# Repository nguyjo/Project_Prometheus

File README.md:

# Walla Walla University Prometheus Rocket Project (2025-2026)

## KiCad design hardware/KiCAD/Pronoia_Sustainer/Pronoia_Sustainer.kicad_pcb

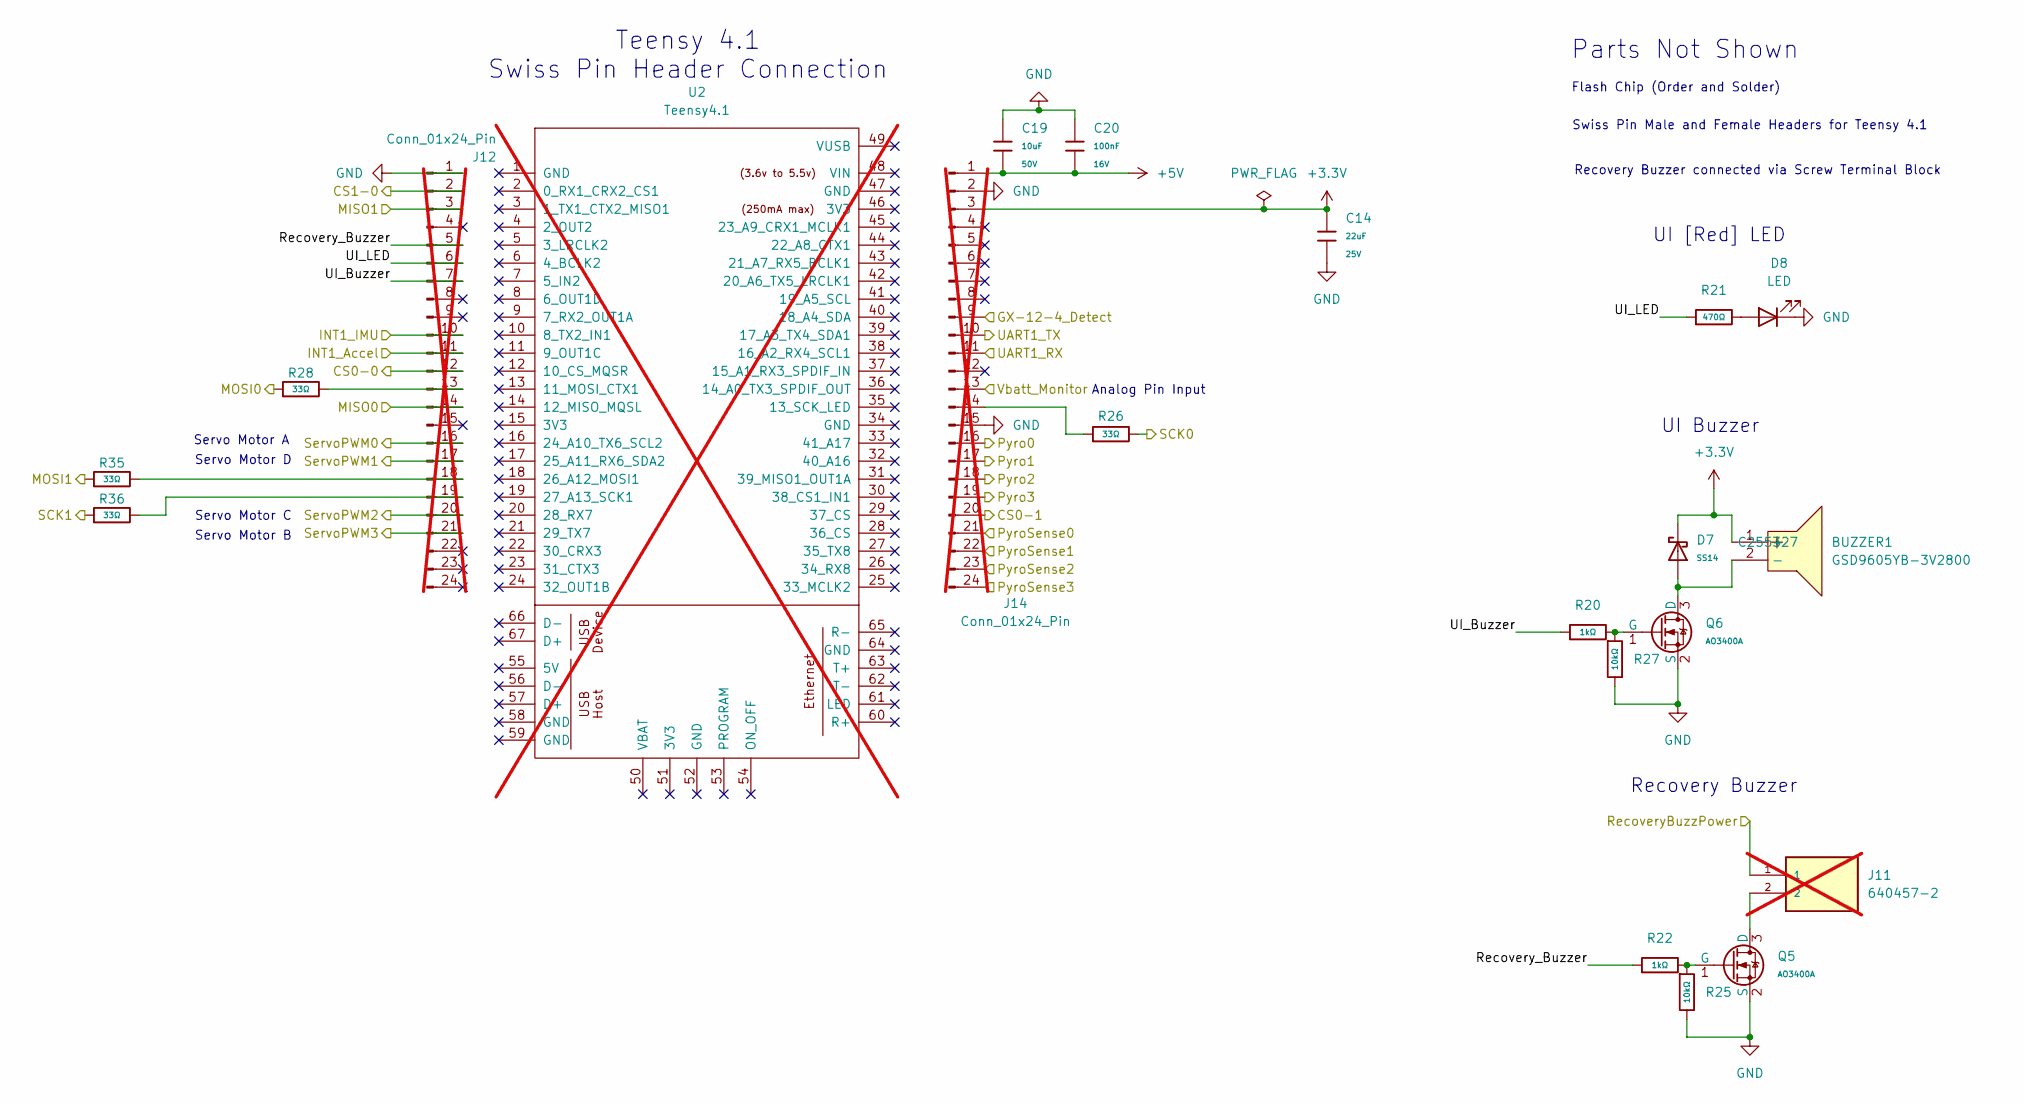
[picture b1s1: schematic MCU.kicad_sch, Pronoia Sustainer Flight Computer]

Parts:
BUZZER1: GSD9605YB-3V2800; BUZ-SMD_GSD9605YB-3V2800; LCSC C255327
C14: 22uF; C_0805; Voltage Rated 25V; Tolerance ±20%; Part CL21A226MAQNNNE; LCSC C45783
C19: 10uF; C_1206; Voltage Rated 50V; Tolerance ±10%; Part CL31A106KBHNNNE; LCSC C13585
C20: 100nF; C_0402; Voltage Rated 16V; Tolerance ±10%; Part CL05B104KO5NNNC; LCSC C1525
D7: SS14; D_SMA; Forward Voltage (Vf@If) 550mV@1A; Reverse Voltage (Vr) 40V; Part SS14; LCSC C2480
D8: LED; LED_0603_1608Metric; LCSC C3030991
J11: 640457-2; TE_640457-2; PARTREV R; not fitted
J12, J14: Conn_01x24_Pin; PinSocket_1x24_P2.54mm_Vertical; not fitted
Q5, Q6: AO3400A; Q_SOT-23; Part AO3400A; LCSC C20917
R20, R22: 1kΩ; R_0805; Overload Voltage (Max) 150V; Tolerance ±1%; Part 0805W8F1001T5E; LCSC C17513
R21: 470Ω; R_0402; Overload Voltage (Max) 50V; Tolerance ±1%; Part 0402WGF4700TCE; LCSC C25117
R25, R27: 10kΩ; R_0805; Overload Voltage (Max) 150V; Tolerance ±1%; Part 0805W8F1002T5E; LCSC C17414
R26, R28, R35, R36: 33Ω; R_0402; Overload Voltage (Max) 50V; Tolerance ±1%; Part 0402WGF330JTCE; LCSC C25105
U2: Teensy4.1; Teensy41; not fitted

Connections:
+3.3V: BUZZER1.1 (+), C14.1, D7.1, J14.3; also elsewhere on the board
+5V: C19.2, C20.1, J14.1; also elsewhere on the board
/Communications/GX-12-4_Detect: J14.9; also elsewhere on the board
/Communications/GX-12-4_RX: J14.10; also elsewhere on the board
/Communications/GX-12-4_TX: J14.11; also elsewhere on the board
/Flight Computer/CS0-0: J12.12; also elsewhere on the board
/Flight Computer/CS0-1: J14.20; also elsewhere on the board
/Flight Computer/CS1-0: J12.2; also elsewhere on the board
/Flight Computer/INT1_Accel: J12.11; also elsewhere on the board
/Flight Computer/INT1_IMU: J12.10; also elsewhere on the board
/Flight Computer/MISO0: J12.14; also elsewhere on the board
/Flight Computer/MISO1: J12.3; also elsewhere on the board
/Flight Computer/MOSI0: R28.1; also elsewhere on the board
/Flight Computer/MOSI1: R35.1; also elsewhere on the board
/Flight Computer/Pyro0: J14.16; also elsewhere on the board
/Flight Computer/Pyro1: J14.17; also elsewhere on the board
/Flight Computer/Pyro2: J14.18; also elsewhere on the board
/Flight Computer/Pyro3: J14.19; also elsewhere on the board
/Flight Computer/PyroSense0: J14.21; also elsewhere on the board
/Flight Computer/PyroSense1: J14.22; also elsewhere on the board
/Flight Computer/PyroSense2: J14.23; also elsewhere on the board
/Flight Computer/PyroSense3: J14.24; also elsewhere on the board
/Flight Computer/RecoveryBuzzPower: J11.1; also elsewhere on the board
/Flight Computer/Recovery_Buzzer: J12.5, R22.1
/Flight Computer/SCK0: R26.2; also elsewhere on the board
/Flight Computer/SCK1: R36.1; also elsewhere on the board
/Flight Computer/ServoPWM0: J12.16; also elsewhere on the board
/Flight Computer/ServoPWM1: J12.17; also elsewhere on the board
/Flight Computer/ServoPWM2: J12.20; also elsewhere on the board
/Flight Computer/ServoPWM3: J12.21; also elsewhere on the board
/Flight Computer/UI_Buzzer: J12.7, R20.1
/Flight Computer/UI_LED: J12.6, R21.1
/Flight Computer/Vbatt_Monitor: J14.13; also elsewhere on the board
GND: C14.2, C19.1, C20.2, D8.1 (K), J12.1, J14.2, J14.15, Q5.2 (S), Q6.2 (S), R25.2, R27.2; also elsewhere on the board
unnamed: BUZZER1.2 (-), D7.2, Q6.3 (D)
unnamed: D8.2 (A), R21.2
unnamed: J12.13, R28.2
unnamed: J12.18, R35.2
unnamed: J12.19, R36.2
unnamed: J14.14, R26.1
unnamed: J11.2, Q5.3 (D)
unnamed: Q5.1 (G), R22.2, R25.1
unnamed: Q6.1 (G), R20.2, R27.1

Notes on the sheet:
Parts Not Shown
Recovery Buzzer connected via Screw Terminal Block
Servo Motor C
Analog Pin Input
Swiss Pin Male and Female Headers for Teensy 4.1
Servo Motor D
Teensy 4.1 Swiss Pin Header Connection
Servo Motor B
Servo Motor A
UI [Red] LED
Flash Chip (Order and Solder)
Recovery Buzzer
UI Buzzer

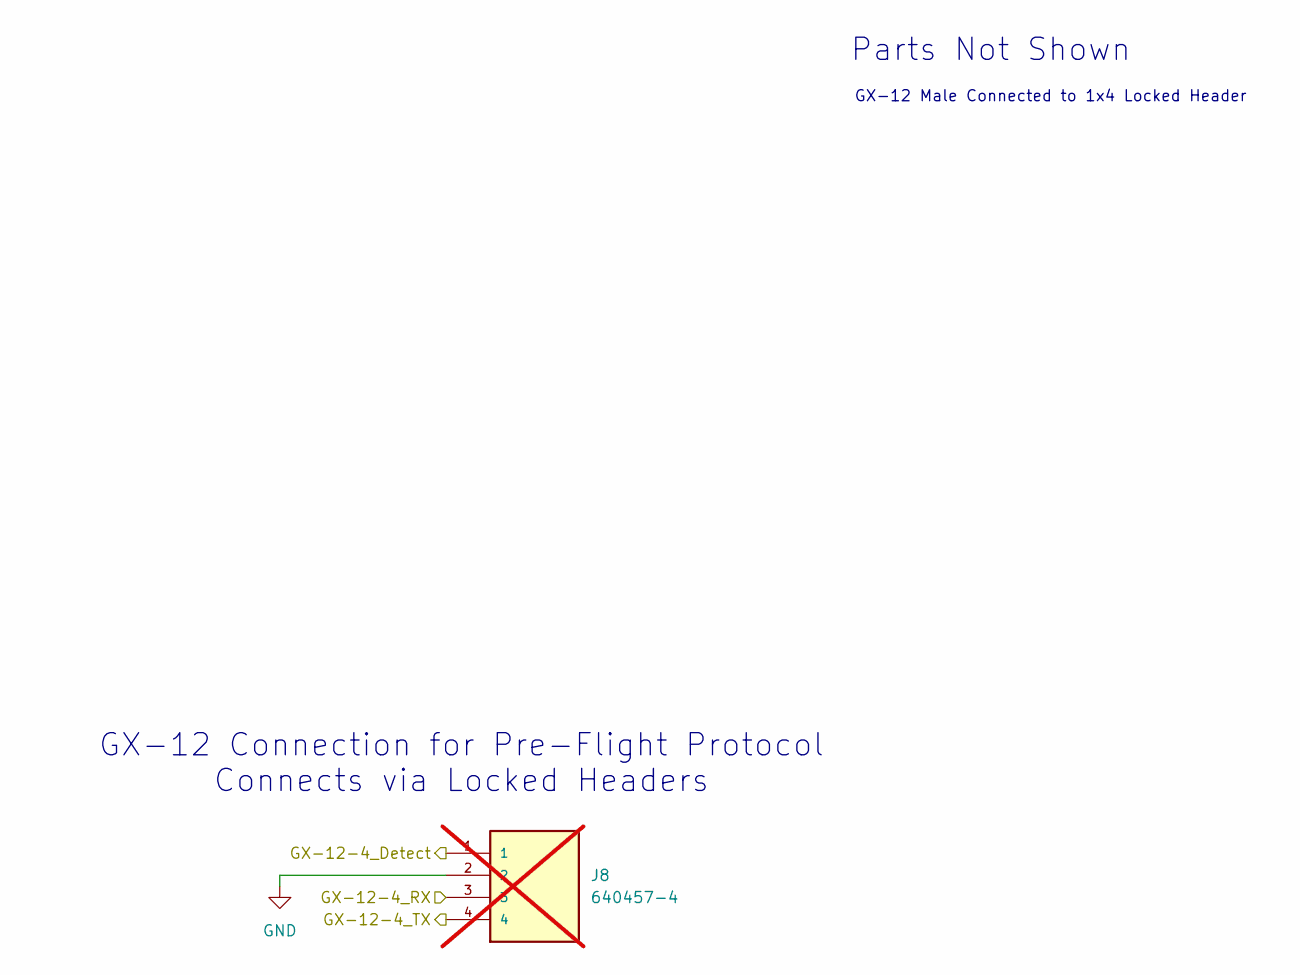
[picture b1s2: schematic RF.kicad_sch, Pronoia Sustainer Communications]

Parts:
J8: 640457-4; TE_640457-4; PARTREV R; not fitted

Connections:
/Communications/GX-12-4_Detect: J8.1; also elsewhere on the board
/Communications/GX-12-4_RX: J8.3; also elsewhere on the board
/Communications/GX-12-4_TX: J8.4; also elsewhere on the board
GND: J8.2; also elsewhere on the board

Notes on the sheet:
GX-12 Connection for Pre-Flight Protocol Connects via Locked Headers
Parts Not Shown
GX-12 Male Connected to 1x4 Locked Header

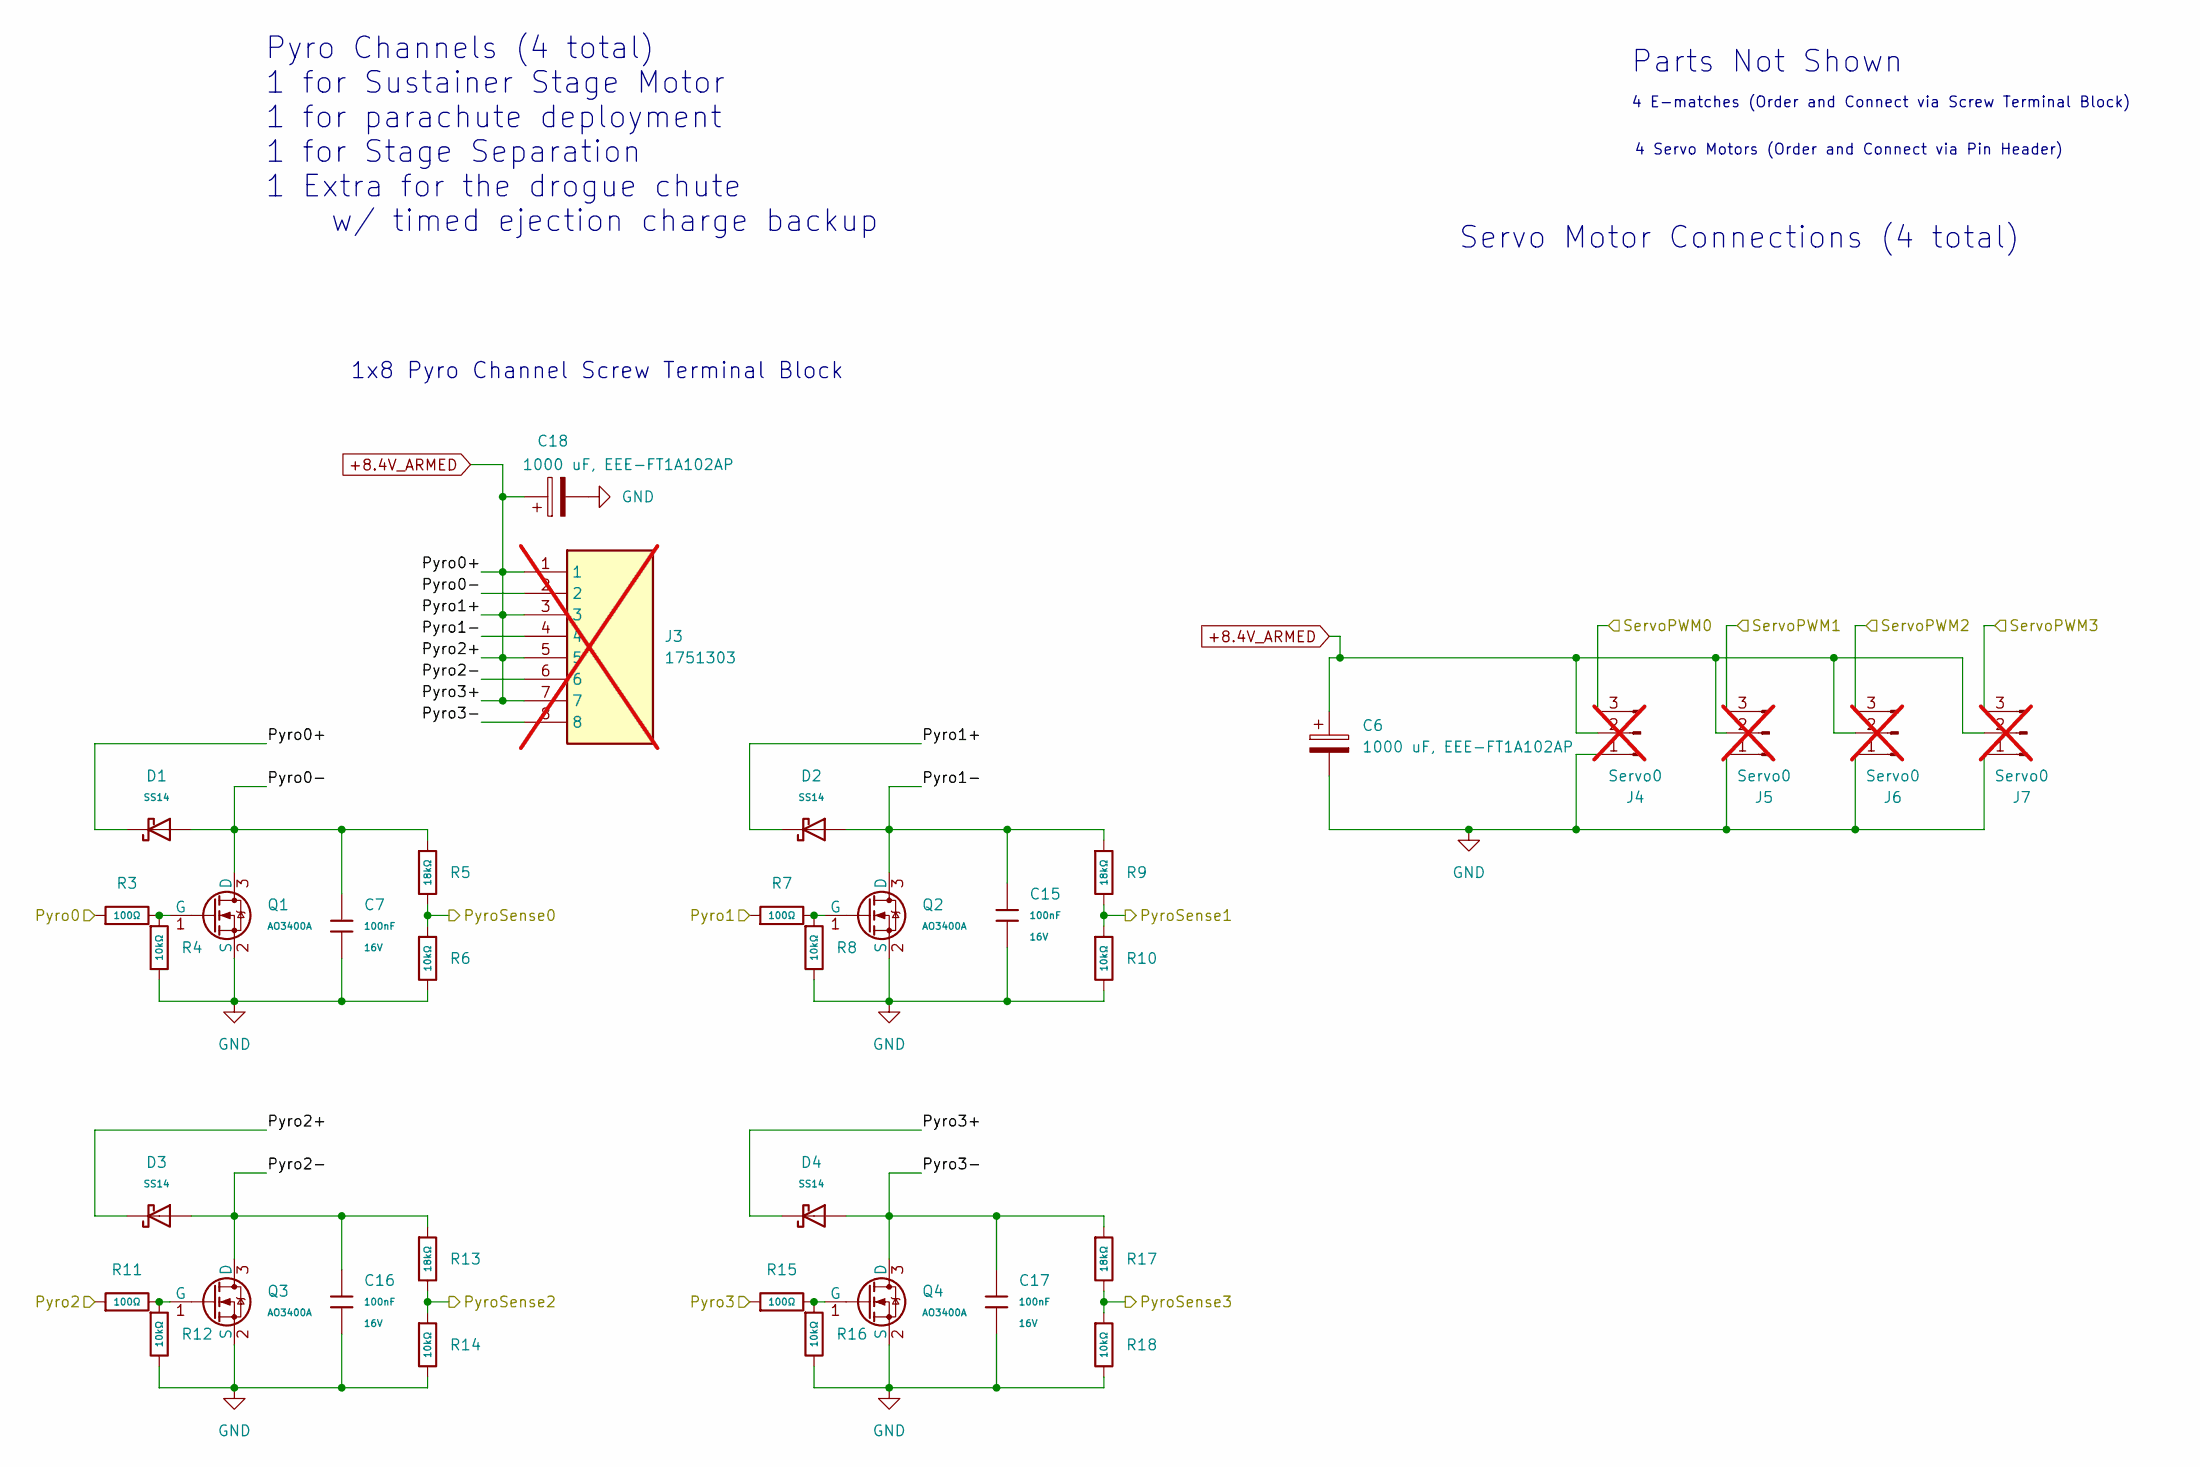
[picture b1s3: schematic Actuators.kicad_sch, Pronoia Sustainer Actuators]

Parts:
C6, C18: 1000 uF, EEE-FT1A102AP; CP_Elec_8x10.5; LCSC C278408
C7, C15, C16, C17: 100nF; C_0402; Voltage Rated 16V; Tolerance ±10%; Part CL05B104KO5NNNC; LCSC C1525
D1, D2, D3, D4: SS14; D_SMA; Forward Voltage (Vf@If) 550mV@1A; Reverse Voltage (Vr) 40V; Part SS14; LCSC C2480
J3: 1751303; Manufacturer_Part_Number 1751303; Mouser Part Number 651-1751303; not fitted
J4, J5, J6, J7: Servo0; PinHeader_1x03_P2.54mm_Vertical; not fitted
Q1, Q2, Q3, Q4: AO3400A; Q_SOT-23; Part AO3400A; LCSC C20917
R3, R7, R11, R15: 100Ω; R_0805; Overload Voltage (Max) 150V; Tolerance ±1%; Part 0805W8F1000T5E; LCSC C17408
R4, R6, R8, R10, R12, R14, R16, R18: 10kΩ; R_0805; Overload Voltage (Max) 150V; Tolerance ±1%; Part 0805W8F1002T5E; LCSC C17414
R5, R9, R13, R17: 18kΩ; R_0603; Overload Voltage (Max) 75V; Tolerance ±1%; Part 0603WAF1802T5E; LCSC C25810

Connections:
+8.4V_ARMED: C6.1, C18.1, D1.1, D2.1, D3.1, D4.1, J3.1, J3.3, J3.5, J3.7, J4.2, J5.2, J6.2, J7.2; also elsewhere on the board
/Flight Computer/Pyro0: R3.1; also elsewhere on the board
/Flight Computer/Pyro1: R7.1; also elsewhere on the board
/Flight Computer/Pyro2: R11.1; also elsewhere on the board
/Flight Computer/Pyro3: R15.1; also elsewhere on the board
/Flight Computer/PyroSense0: R5.2, R6.1; also elsewhere on the board
/Flight Computer/PyroSense1: R9.2, R10.1; also elsewhere on the board
/Flight Computer/PyroSense2: R13.2, R14.1; also elsewhere on the board
/Flight Computer/PyroSense3: R17.2, R18.1; also elsewhere on the board
/Flight Computer/ServoPWM0: J4.3; also elsewhere on the board
/Flight Computer/ServoPWM1: J5.3; also elsewhere on the board
/Flight Computer/ServoPWM2: J6.3; also elsewhere on the board
/Flight Computer/ServoPWM3: J7.3; also elsewhere on the board
/High-Power Actuators/Pyro0-: C7.1, D1.2, J3.2, Q1.3 (D), R5.1
/High-Power Actuators/Pyro1-: C15.1, D2.2, J3.4, Q2.3 (D), R9.1
/High-Power Actuators/Pyro2-: C16.1, D3.2, J3.6, Q3.3 (D), R13.1
/High-Power Actuators/Pyro3-: C17.1, D4.2, J3.8, Q4.3 (D), R17.1
GND: C6.2, C7.2, C15.2, C16.2, C17.2, C18.2, J4.1, J5.1, J6.1, J7.1, Q1.2 (S), Q2.2 (S), Q3.2 (S), Q4.2 (S), R4.2, R6.2, R8.2, R10.2, R12.2, R14.2, R16.2, R18.2; also elsewhere on the board
unnamed: Q1.1 (G), R3.2, R4.1
unnamed: Q2.1 (G), R7.2, R8.1
unnamed: Q3.1 (G), R11.2, R12.1
unnamed: Q4.1 (G), R15.2, R16.1

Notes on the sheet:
4 E-matches (Order and Connect via Screw Terminal Block)
Parts Not Shown
Pyro Channels (4 total) 1 for Sustainer Stage Motor 1 for parachute deployment 1 for Stage Separation 1 Extra for the drogue chute w/ timed ejection charge backup
1x8 Pyro Channel Screw Terminal Block
4 Servo Motors (Order and Connect via Pin Header)
Servo Motor Connections (4 total)

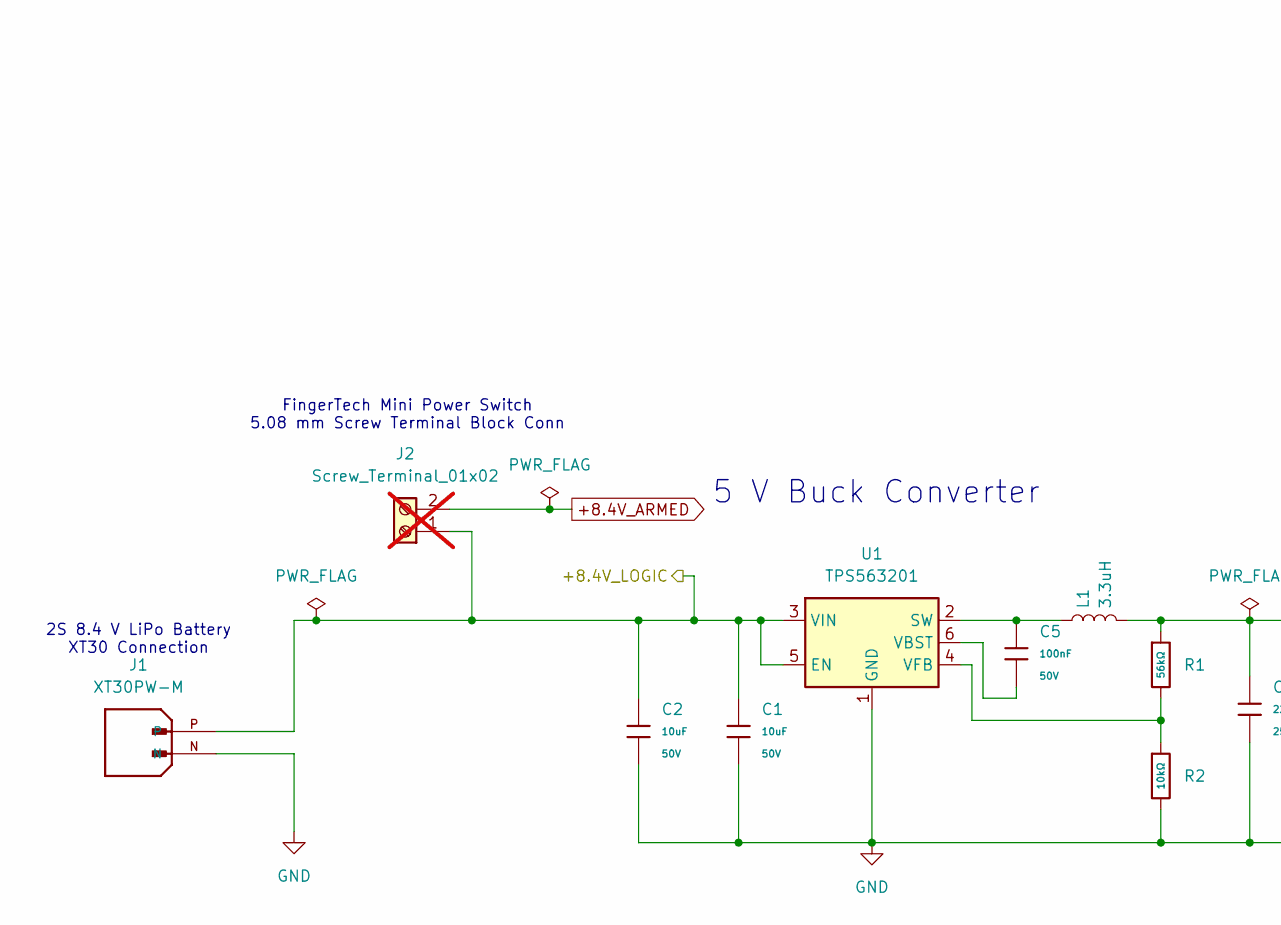
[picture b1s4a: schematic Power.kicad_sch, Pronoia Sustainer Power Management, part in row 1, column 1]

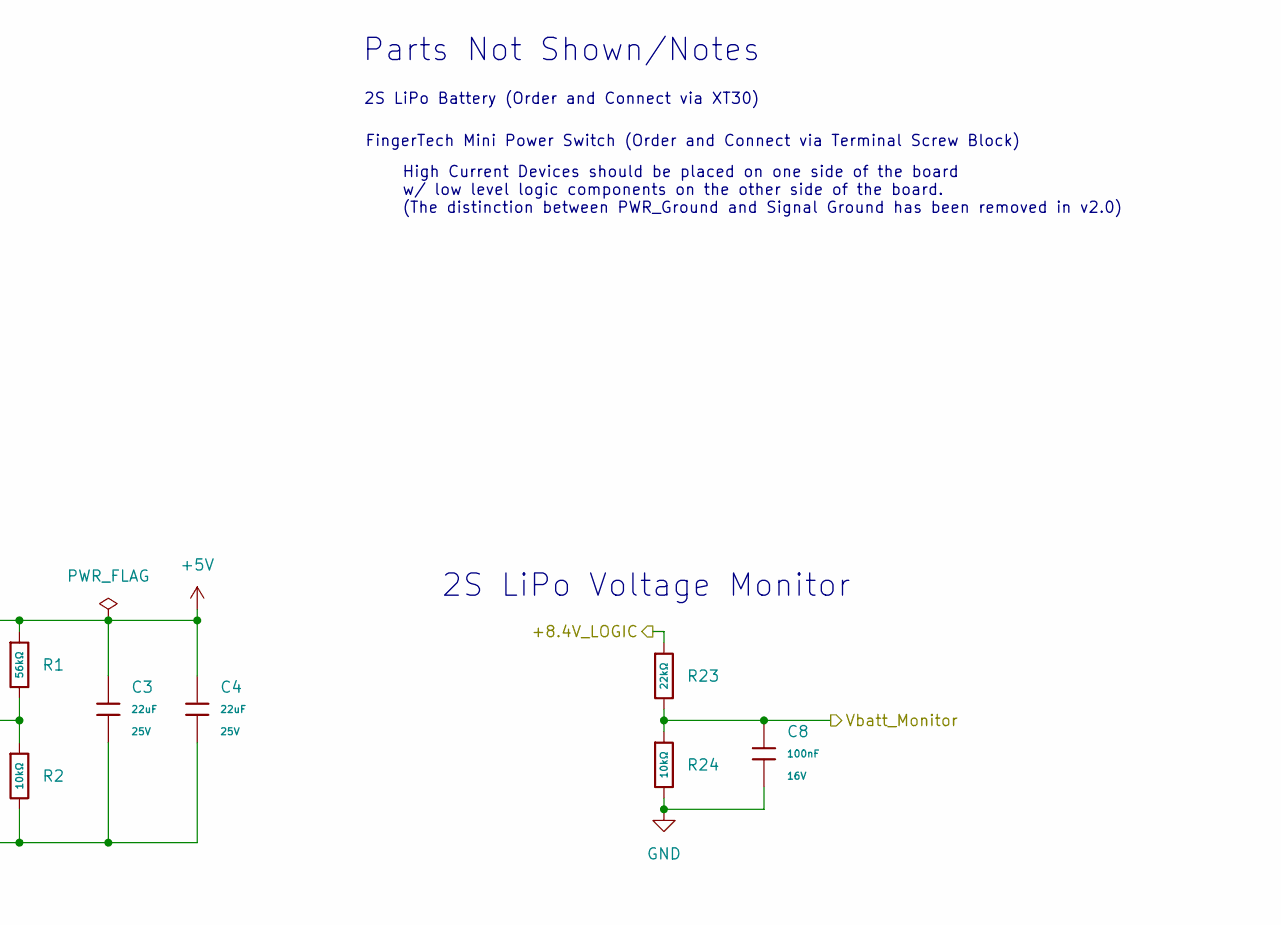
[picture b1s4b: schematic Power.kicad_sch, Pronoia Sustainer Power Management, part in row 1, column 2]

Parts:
C1, C2: 10uF; C_1206; Voltage Rated 50V; Tolerance ±10%; Part CL31A106KBHNNNE; LCSC C13585
C3, C4: 22uF; C_0805; Voltage Rated 25V; Tolerance ±20%; Part CL21A226MAQNNNE; LCSC C45783
C5: 100nF; C_1206; Voltage Rated 50V; Tolerance ±10%; Part CL31B104KBCNNNC; LCSC C24497
C8: 100nF; C_0402; Voltage Rated 16V; Tolerance ±10%; Part CL05B104KO5NNNC; LCSC C1525
J1: XT30PW-M; AMASS_XT30PW-M; PARTREV 1.2; LCSC C431092
J2: Screw_Terminal_01x02; TerminalBlock_Phoenix_MKDS-1,5-2-5.08_1x02_P5.08mm_Horizont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; not fitted
L1: 3.3uH; L_Bourns-SRN8040_8x8.15mm; LCSC C780188
R1: 56kΩ; R_0603; Overload Voltage (Max) 75V; Tolerance ±1%; Part 0603WAF5602T5E; LCSC C23206
R2: 10kΩ; R_0603; Overload Voltage (Max) 75V; Tolerance ±1%; Part 0603WAF1002T5E; LCSC C25804
R23: 22kΩ; R_0805; Overload Voltage (Max) 150V; Tolerance ±1%; Part 0805W8F2202T5E; LCSC C17560
R24: 10kΩ; R_0805; Overload Voltage (Max) 150V; Tolerance ±1%; Part 0805W8F1002T5E; LCSC C17414
U1: TPS563201; SOT-23-6; LCSC C116592

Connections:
+5V: C3.1, C4.1, L1.2, R1.1; also elsewhere on the board
+8.4V_ARMED: J2.2; also elsewhere on the board
/Flight Computer/RecoveryBuzzPower: C1.1, C2.1, J1.P, J2.1, R23.1, U1.3 (VIN), U1.5 (EN); also elsewhere on the board
/Flight Computer/Vbatt_Monitor: C8.1, R23.2, R24.1; also elsewhere on the board
GND: C1.2, C2.2, C3.2, C4.2, C8.2, J1.N, R2.2, R24.2, U1.1 (GND); also elsewhere on the board
unnamed: C5.1, L1.1, U1.2 (SW)
unnamed: C5.2, U1.6 (VBST)
unnamed: R1.2, R2.1, U1.4 (VFB)

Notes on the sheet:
5 V Buck Converter
FingerTech Mini Power Switch 5.08 mm Screw Terminal Block Conn
2S LiPo Voltage Monitor
High Current Devices should be placed on one side of the board w/ low level logic components on the other side of the board. (The distinction between PWR_Ground and Signal Ground has been removed in v2.0)
2S 8.4 V LiPo Battery XT30 Connection
2S LiPo Battery (Order and Connect via XT30)
FingerTech Mini Power Switch (Order and Connect via Terminal Screw Block)
Parts Not Shown/Notes

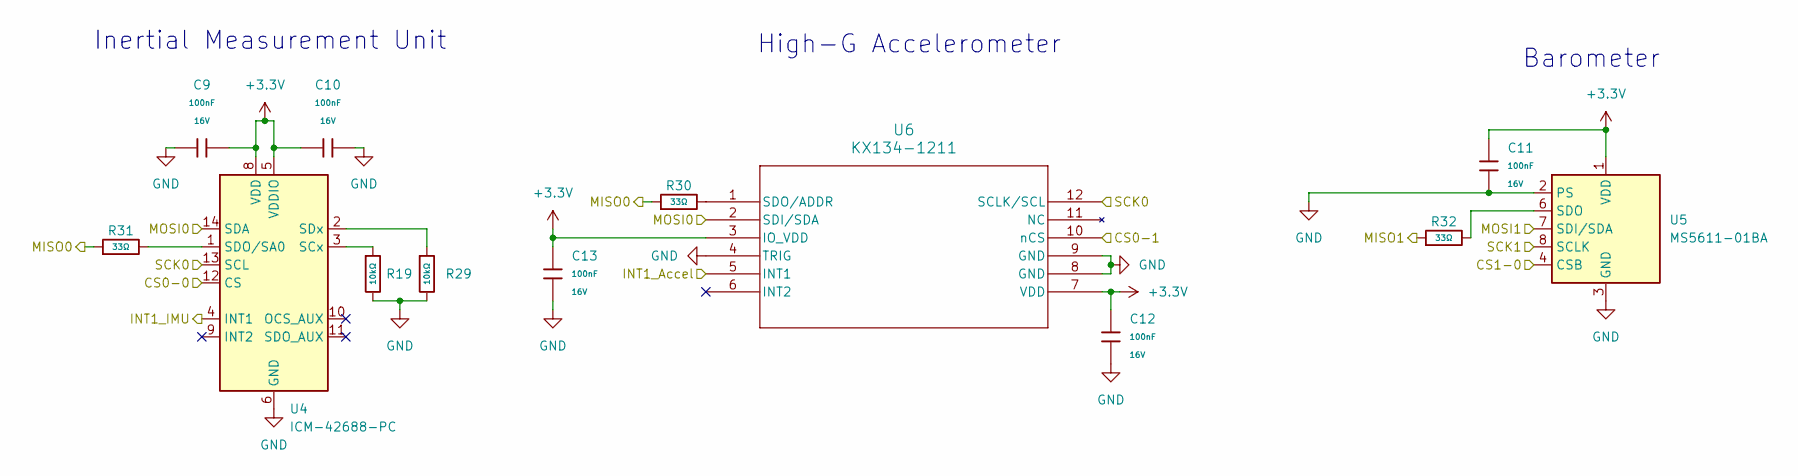
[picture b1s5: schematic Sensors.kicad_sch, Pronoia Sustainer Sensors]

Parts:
C9, C10, C11, C12, C13: 100nF; C_0402; Voltage Rated 16V; Tolerance ±10%; Part CL05B104KO5NNNC; LCSC C1525
R19, R29: 10kΩ; R_0805; Overload Voltage (Max) 150V; Tolerance ±1%; Part 0805W8F1002T5E; LCSC C17414
R30, R31, R32: 33Ω; R_0402; Overload Voltage (Max) 50V; Tolerance ±1%; Part 0402WGF330JTCE; LCSC C25105
U4: ICM-42688-PC; LGA-14_3x2.5mm_P0.5mm_LayoutBorder3x4y; LCSC C48586483
U5: MS5611-01BA; LGA-8_3x5mm_P1.25mm; LCSC C15639
U6: KX134-1211; KIONIX_KXTJ3-1057; LCSC C2157908

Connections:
+3.3V: C9.2, C10.1, C11.2, C12.2, C13.2, U4.5 (VDDIO), U4.8 (VDD), U5.1 (VDD), U6.3 (IO_VDD), U6.7 (VDD); also elsewhere on the board
/Flight Computer/CS0-0: U4.12 (CS); also elsewhere on the board
/Flight Computer/CS0-1: U6.10 (nCS); also elsewhere on the board
/Flight Computer/CS1-0: U5.4 (CSB), U5.5 (CSB); also elsewhere on the board
/Flight Computer/INT1_Accel: U6.5 (INT1); also elsewhere on the board
/Flight Computer/INT1_IMU: U4.4 (INT1); also elsewhere on the board
/Flight Computer/MISO0: R30.1, R31.1; also elsewhere on the board
/Flight Computer/MISO1: R32.1; also elsewhere on the board
/Flight Computer/MOSI0: U4.14 (SDA), U6.2 (SDI/SDA); also elsewhere on the board
/Flight Computer/MOSI1: U5.7 (SDI/SDA); also elsewhere on the board
/Flight Computer/SCK0: U4.13 (SCL), U6.12 (SCLK/SCL); also elsewhere on the board
/Flight Computer/SCK1: U5.8 (SCLK); also elsewhere on the board
GND: C9.1, C10.2, C11.1, C12.1, C13.1, R19.2, R29.2, U4.6 (GND), U4.7 (GND), U5.2 (PS), U5.3 (GND), U6.4 (TRIG), U6.8 (GND), U6.9 (GND); also elsewhere on the board
unnamed: R19.1, U4.3 (SCx)
unnamed: R31.2, U4.1 (SDO/SA0)
unnamed: R29.1, U4.2 (SDx)
unnamed: R32.2, U5.6 (SDO)
unnamed: R30.2, U6.1 (SDO/ADDR)

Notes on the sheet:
High-G Accelerometer
Barometer
Inertial Measurement Unit

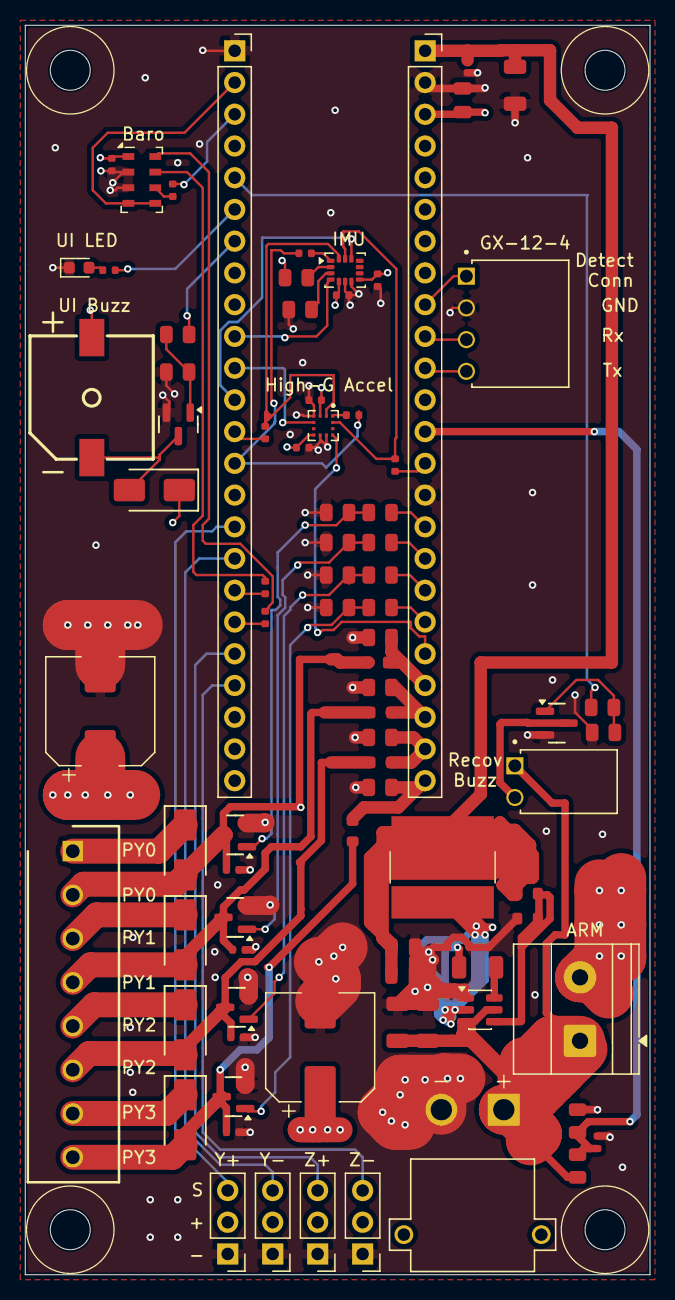
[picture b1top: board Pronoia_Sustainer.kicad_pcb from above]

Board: 4 copper layers, 50.0 x 100.0 mm, 83 parts (0 on the bottom side), 60 nets.

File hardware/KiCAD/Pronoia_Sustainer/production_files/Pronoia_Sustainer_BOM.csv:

Reference,Value,Footprint,LCSC
BUZZER1,GSD9605YB-3V2800,GSD9605YB-3V2800:BUZ-SMD_GSD9605YB-3V2800,C255327
"C1,C2,C19",10uF,PCM_JLCPCB:C_1206,C13585
"C3,C4,C14",22uF,PCM_JLCPCB:C_0805,C45783
C5,100nF,PCM_JLCPCB:C_1206,C24497
"C6,C18","1000 uF, EEE-FT1A102AP",Capacitor_SMD:CP_Elec_8x10.5,C278408
"C7,C8,C9,C10,C11,C12,C13,C15,C16,C17,C20",100nF,PCM_JLCPCB:C_0402,C1525
"D1,D2,D3,D4,D7",SS14,PCM_JLCPCB:D_SMA,C2480
D8,LED,LED_SMD:LED_0603_1608Metric,C3030991
J1,XT30PW-M,XT30PW-M:AMASS_XT30PW-M,C431092
J2,Screw_Terminal_01x02,"TerminalBlock_Phoenix:TerminalBlock_Phoenix_MKDS-1,5-2-5.08_1x02_P5.08mm_Horizontal",
J3,1751303,1751303:1751303,
"J4,J5,J6,J7",Servo0,Connector_PinHeader_2.54mm:PinHeader_1x03_P2.54mm_Vertical,
J8,640457-4,640457-4:TE_640457-4,
J11,640457-2,640457-2:TE_640457-2,
"J12,J14",Conn_01x24_Pin,Connector_PinSocket_2.54mm:PinSocket_1x24_P2.54mm_Vertical,
L1,3.3uH,Inductor_SMD:L_Bourns-SRN8040_8x8.15mm,C780188
"Q1,Q2,Q3,Q4,Q5,Q6",AO3400A,PCM_JLCPCB:Q_SOT-23,C20917
R1,56kΩ,PCM_JLCPCB:R_0603,C23206
R2,10kΩ,PCM_JLCPCB:R_0603,C25804
"R3,R7,R11,R15",100Ω,PCM_JLCPCB:R_0805,C17408
"R4,R6,R8,R10,R12,R14,R16,R18,R19,R24,R25,R27,R29",10kΩ,PCM_JLCPCB:R_0805,C17414
"R5,R9,R13,R17",18kΩ,PCM_JLCPCB:R_0603,C25810
"R20,R22",1kΩ,PCM_JLCPCB:R_0805,C17513
R21,470Ω,PCM_JLCPCB:R_0402,C25117
R23,22kΩ,PCM_JLCPCB:R_0805,C17560
"R26,R28,R30,R31,R32,R35,R36",33Ω,PCM_JLCPCB:R_0402,C25105
U1,TPS563201,Package_TO_SOT_SMD:SOT-23-6,C116592
U2,Teensy4.1,teensy.pretty-master:Teensy41,
U4,ICM-42688-PC,Package_LGA:LGA-14_3x2.5mm_P0.5mm_LayoutBorder3x4y,C48586483
U5,MS5611-01BA,Package_LGA:LGA-8_3x5mm_P1.25mm,C15639
U6,KX134-1211,KX134-1211:KIONIX_KXTJ3-1057,C2157908

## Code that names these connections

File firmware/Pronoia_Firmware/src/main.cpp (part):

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StateEstimator estimator(accelSrc, baro);
 
// Pyro channels — one per physical pyro output
PyroChannel pyro0(Config::Pins::PYRO0_FIRE, Config::Pins::PYRO0_CONT, "PYRO0");
PyroChannel pyro1(Config::Pins::PYRO1_FIRE, Config::Pins::PYRO1_CONT, "PYRO1");
PyroChannel pyro2(Config::Pins::PYRO2_FIRE, Config::Pins::PYRO2_CONT, "PYRO2");
PyroChannel pyro3(Config::Pins::PYRO3_FIRE, Config::Pins::PYRO3_CONT, "PYRO3");
 
// Buzzers
Buzzer uiBuzzer(Config::Pins::UI_BUZZER, "UI");
Buzzer recoveryBuzzer(Config::Pins::RECOVERY_BUZZER, "RECOVERY");
 
// Battery monitor
BatteryMonitor batteryMonitor(Config::Pins::VBATT_MONITOR_PIN);

FlashLogger flashLogger;
 
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
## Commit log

2026-01-22 Initial Setup: .gitignore
2026-01-23 Added .gitignore and created KiCAD projects
2026-01-24 Initial start for Pronoia Schematic
2026-01-25 Added 1st Pyro Channel w/ Continuity Testing
2026-01-26 Added Servo Motor PWM Pin Headers and Electrolytic Capacitor
2026-01-29 PyroChannel LTSpice Confirmation, Added LDO Regulator, Heirarchical Sheet
2026-01-29 Added footprints to all placed symbols
2026-01-30 Added PyroChannel Sim, Organized directory
2026-01-30 Added IMU and connections
2026-01-31 Added communication symbols to schematic
2026-02-02 Completed 1st Draft
2026-02-04 updated Schematics
2026-02-04 Completed 1st draft of Schematic
2026-02-20 Last commit for KiCAD schematic w/ GPS, Telem, and Bluetooth
2026-03-02 Red LED and UI Buzzer Circuit
2026-03-04 Finalized v2.0 of Pronoia Schematic
2026-03-12 Finished PCB layout
2026-04-28 Sensor Bring-Up
2026-05-01 Driver codes; axis orientation verified
2026-05-02 Barometer-based Velocity Estimate
2026-06-22 Updated codebase
2026-06-22 Prometheus Project Final Paper
2026-06-22 Prometheus Project Posters
2026-06-22 Prometheus Project Final Presentation
2026-06-22 Prometheus BOM Master
2026-06-22 External Parts BOM
2026-06-22 Energy Budget Calculation
2026-06-22 Energy Budget Calculation update
2026-06-22 README start
